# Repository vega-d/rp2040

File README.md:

# rp2040-nano
 Raspberry Pi Pico board but in a formfactor allowing for easier integration.

**Dimensions:** 25x25 mm.

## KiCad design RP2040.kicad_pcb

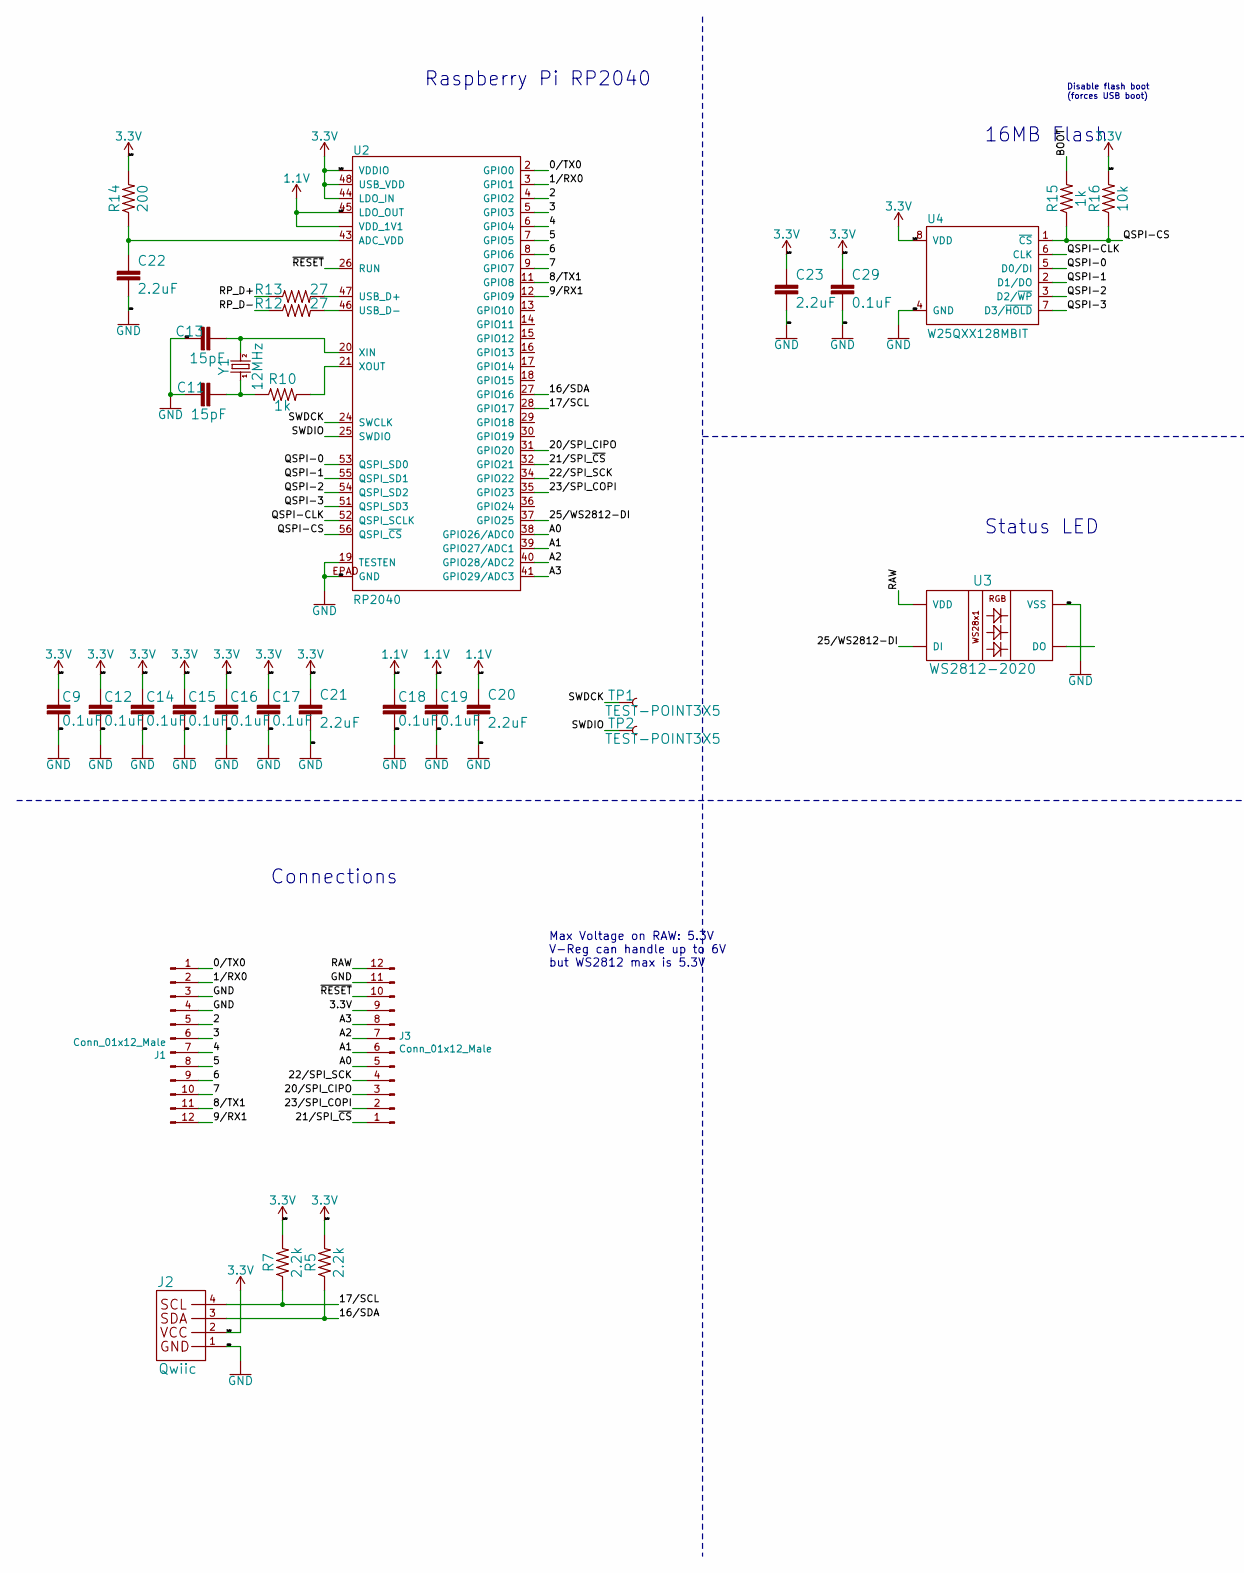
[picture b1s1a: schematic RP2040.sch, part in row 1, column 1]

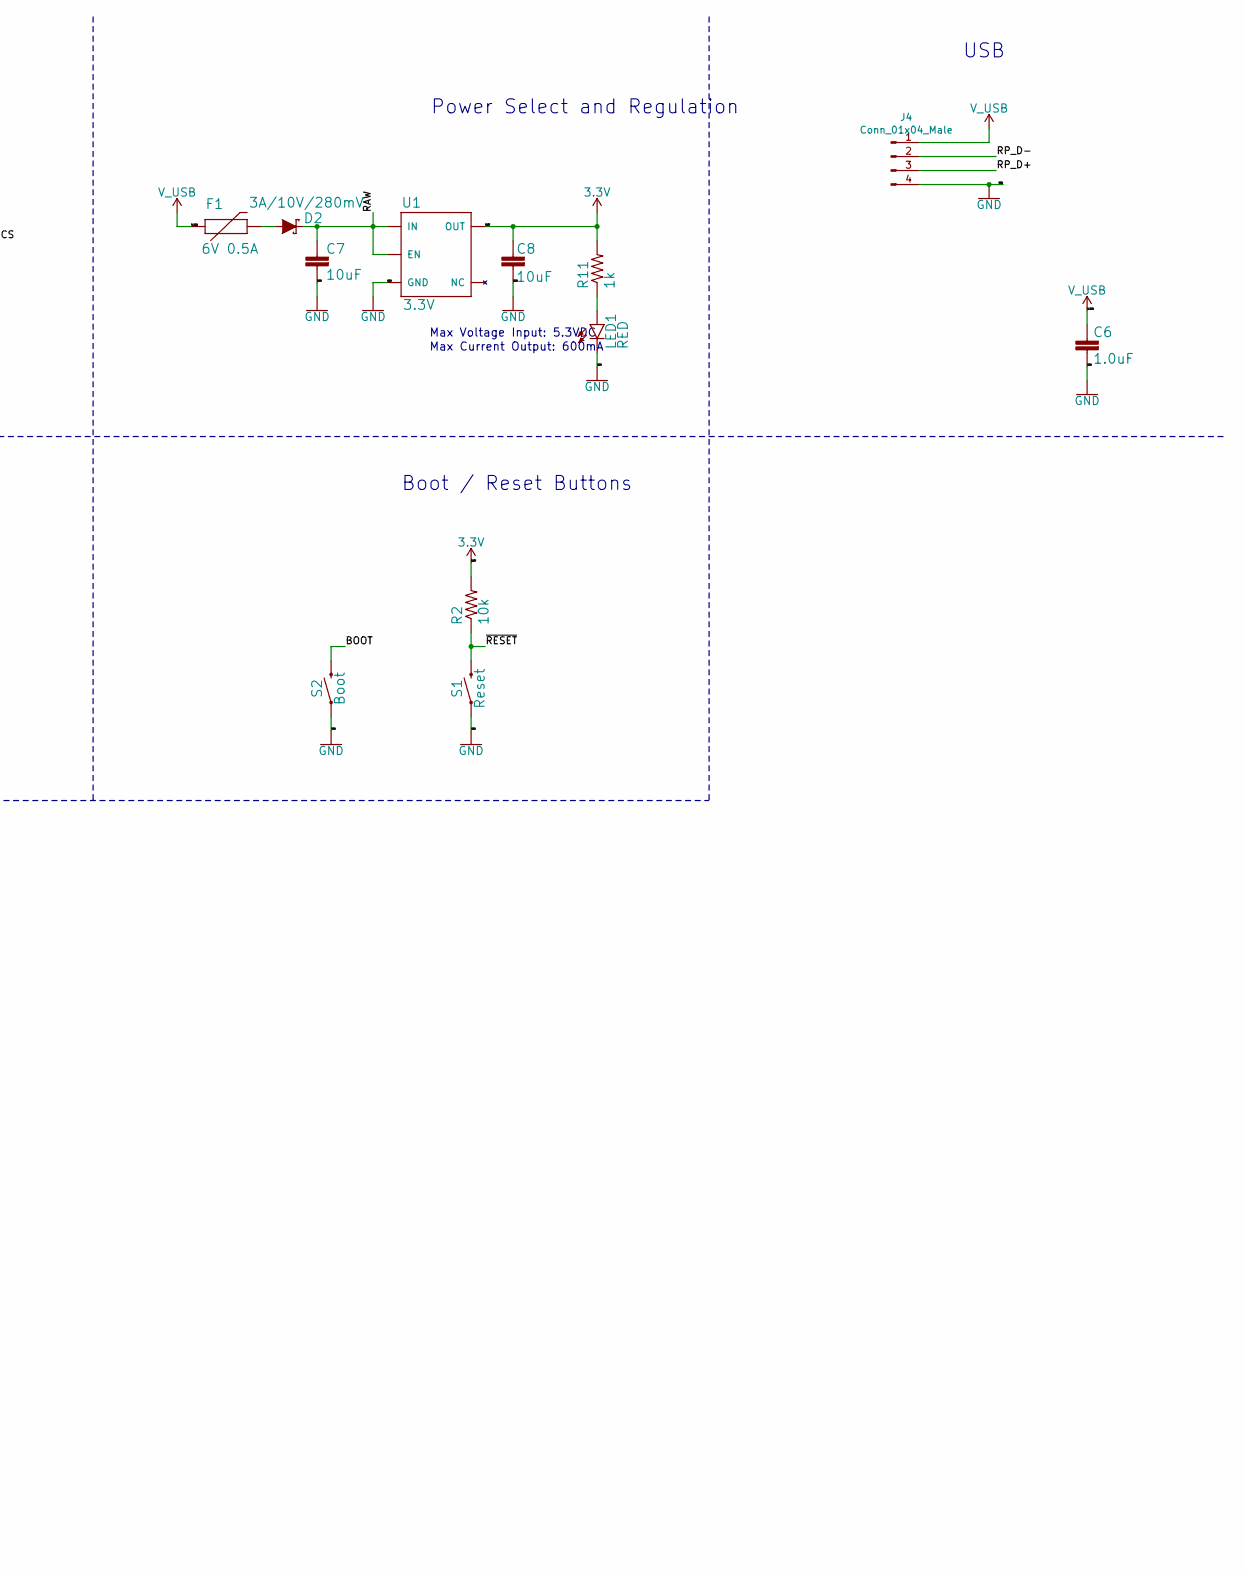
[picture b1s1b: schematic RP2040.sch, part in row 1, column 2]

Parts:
C6: 1.0uF; 0402-TIGHT
C7, C8: 10uF; 0402-TIGHT
C9, C12, C14, C15, C16, C17, C18, C19, C29: 0.1uF; 0402-TIGHT
C11, C13: 15pF; 0402-TIGHT
C20, C21, C22, C23: 2.2uF; 0402-TIGHT
D2: 3A/10V/280mV; SOD-323
F1: 6V 0.5A; 0805
J1, J3: Conn_01x12_Male; PinSocket_2x06_P1.27mm_Vertical_SMD
J2: Qwiic; JST04_1MM_RA
J4: Conn_01x04_Male; PinSocket_2x06_P1.27mm_Vertical_SMD
LED1: RED; LED-0603
R2, R16: 10k; 0402-TIGHT
R5, R7: 2.2k; 0402-TIGHT
R10, R11, R15: 1k; 0402-TIGHT
R12, R13: 27; 0402-TIGHT
R14: 200; 0402-TIGHT
S1: Reset; TACTILE_SWITCH_SMD_4.6X2.8MM
S2: Boot; TACTILE_SWITCH_SMD_4.6X2.8MM
TP1, TP2: TEST-POINT3X5; PAD.03X.05
U1: 3.3V; SOT23-5
U2: RP2040; QFN-56
U3: WS2812-2020
U4: W25QXX128MBIT; WSON-8-6X5-SKINNY_CENTERPAD
Y1: 12MHz; CRYSTAL-SMD-2X2.5MM

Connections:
1.1V: C18.1, C19.1, C20.1, U2.23 (VDD_1V1), U2.45 (LDO_OUT), U2.50 (VDD_1V1)
3.3V: C8.2, C9.1, C12.1, C14.1, C15.1, C16.1, C17.1, C21.1, C23.1, C29.1, J2.2, J3.9, R2.2, R5.2, R7.2, R11.2, R14.2, R16.2, U1.5 (OUT), U2.1 (VDDIO), U2.10 (VDDIO), U2.22 (VDDIO), U2.33 (VDDIO), U2.42 (VDDIO), U2.44 (LDO_IN), U2.48 (USB_VDD), U2.49 (VDDIO), U4.8 (VDD)
/0/TX0: J1.1, U2.2 (GPIO0)
/1/RX0: J1.2, U2.3 (GPIO1)
/2: J1.5, U2.4 (GPIO2)
/3: J1.6, U2.5 (GPIO3)
/4: J1.7, U2.6 (GPIO4)
/5: J1.8, U2.7 (GPIO5)
/6: J1.9, U2.8 (GPIO6)
/7: J1.10, U2.9 (GPIO7)
/8/TX1: J1.11, U2.11 (GPIO8)
/9/RX1: J1.12, U2.12 (GPIO9)
/16/SDA: J2.3, R5.1, U2.27 (GPIO16)
/17/SCL: J2.4, R7.1, U2.28 (GPIO17)
/20/SPI_CIPO: J3.3, U2.31 (GPIO20)
/21/SPI_~CS~: J3.1, U2.32 (GPIO21)
/22/SPI_SCK: J3.4, U2.34 (GPIO22)
/23/SPI_COPI: J3.2, U2.35 (GPIO23)
/25/WS2812-DI: U2.37 (GPIO25), U3.3 (DI)
/A0: J3.5, U2.38 (GPIO26/ADC0)
/A1: J3.6, U2.39 (GPIO27/ADC1)
/A2: J3.7, U2.40 (GPIO28/ADC2)
/A3: J3.8, U2.41 (GPIO29/ADC3)
/BOOT: R15.2, S2.3 (2), S2.4 (2)
/QSPI-0: U2.53 (QSPI_SD0), U4.5 (D0/DI)
/QSPI-1: U2.55 (QSPI_SD1), U4.2 (D1/DO)
/QSPI-2: U2.54 (QSPI_SD2), U4.3 (D2/~WP~)
/QSPI-3: U2.51 (QSPI_SD3), U4.7 (D3/~HOLD~)
/QSPI-CLK: U2.52 (QSPI_SCLK), U4.6 (CLK)
/QSPI-CS: R15.1, R16.1, U2.56 (QSPI_~CS~), U4.1 (~CS~)
/RAW: C7.2, D2.C, J3.12, U1.1 (IN), U1.3 (EN), U3.4 (VDD)
/RP_D+: J4.3, R13.1
/RP_D-: J4.2, R12.1
/SWDCK: TP1.P$1, U2.24 (SWCLK)
/SWDIO: TP2.P$1, U2.25 (SWDIO)
/~RESET~: J3.10, R2.1, S1.3 (2), S1.4 (2), U2.26 (RUN)
GND: C6.1, C7.1, C8.1, C9.2, C11.1, C12.2, C13.1, C14.2, C15.2, C16.2, C17.2, C18.2, C19.2, C20.2, C21.2, C22.2, C23.2, C29.2, J1.3, J1.4, J2.1, J3.11, J4.4, LED1.C, S1.1, S1.2 (1), S2.1, S2.2 (1), U1.2 (GND), U2.19 (TESTEN), U2.EPAD (GND), U3.2 (VSS), U4.4 (GND)
unnamed: C11.2, R10.1, Y1.P1 (1)
unnamed: C13.2, U2.20 (XIN), Y1.P3 (2)
unnamed: C22.1, R14.1, U2.43 (ADC_VDD)
unnamed: D2.A, F1.2
unnamed: LED1.A, R11.1
unnamed: R10.2, U2.21 (XOUT)
unnamed: R12.2, U2.46 (USB_D-)
unnamed: R13.2, U2.47 (USB_D+)
V_USB: C6.2, F1.1, J4.1

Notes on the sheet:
Max Voltage Input: 5.3VDC
Max Current Output: 600mA
Raspberry Pi RP2040
16MB Flash
Disable flash boot (forces USB boot)
Status LED
Power Select and Regulation
USB
Connections
Boot / Reset Buttons
Max Voltage on RAW: 5.3V V-Reg can handle up to 6V but WS2812 max is 5.3V

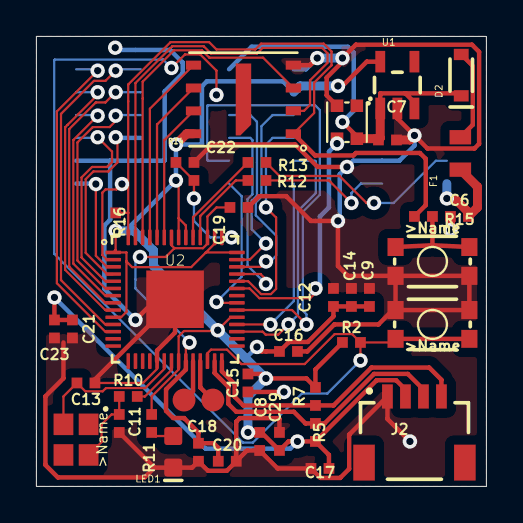
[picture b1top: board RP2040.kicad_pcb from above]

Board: 4 copper layers, 25.0 x 25.0 mm, 44 parts (0 on the bottom side), 46 nets.

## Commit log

2021-09-25 removed obsolete files
2021-09-25 fixed file naming
